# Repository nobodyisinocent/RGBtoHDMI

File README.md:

# Table of contents
1. [What is the RGBtoHDMI board](#1)
2. [Tiny RGB2HDMI CPLD design](#2)
3. [Low profile board based on design from c0pperdragon](#3)
    1. [CTDV board !](#3.1)
    2. [AMIGA 500 boards](#3.2)

# What is the RGBtoHDMI board 
The RGBtoHDMI device adds an HDMI output to your AMIGA only in OCS display mode thanks to the use of a Raspberry Pi0.
The very first RGB2HDMI design has been made by c0pperdragon. It can be found here:

https://github.com/c0pperdragon/Amiga-Digital-Video/

Originally, I made my own version since I wanted the smallest possible pcb for my personnal use, and also for the use of my friend Lolof.
The aim of these designs is to allow the combined use of the RGB2HDMI and others expansions as accelerator boards for example like the big board of the Mega Midget Racer.

Here, you'll find the three lowprofile following versions of the RGBtoHDMI I designed with Kicad and FreeRooting under Linux.

# Tiny RGB2HDMI CPLD design 
Always with the same goal, as small as possible, this board uses the CPLD Rev1.1 design from solarmon. But, since the configuration menu is accessible with one button, the 3 buttons and the OSD connector (no interest for my use) have been removed.

The firmware can be downloaded onto the official Github of the original CPLD version from hoglet67 here:

https://github.com/hoglet67/RGBtoHDMI/releases

To install the firmware, as for the first version of the RGBtoHDMI, simply extract the files to the µ-SD card's root and follow the instruction from Amiga_Readme.txt inside the Amiga_CPLD_Setup directory.

Here some pictures from Lolof of the Tiny CPLD RGBtoHDMI installed onto an A500 with the excellent TK030 from Matze !

# Low profile board based on design from c0pperdragon 

## CDTV board 

Here is the version specially designed for the CDTV.
The goal is always the same,having a nice and small board. :-)

## AMIGA 500 boards 

Two designs versions have been done. Here they are:

First design with Pi0 located between CIA and PAULA:

Second version, the smallest design version with the Pi0 installed just onto CIA with HDMI output on the back of the AMIGA.
It was special request of my friend Lolof, and perhaps the best one of the two A500 design:

And some pictures from Lolof of this second version rgb2hdmi in action onto his A500 !

And the first version onto my A500+ Red edition used with the Vampire V2+!

I hope you'll enjoy these versions of this great device !

-Tuxbar81

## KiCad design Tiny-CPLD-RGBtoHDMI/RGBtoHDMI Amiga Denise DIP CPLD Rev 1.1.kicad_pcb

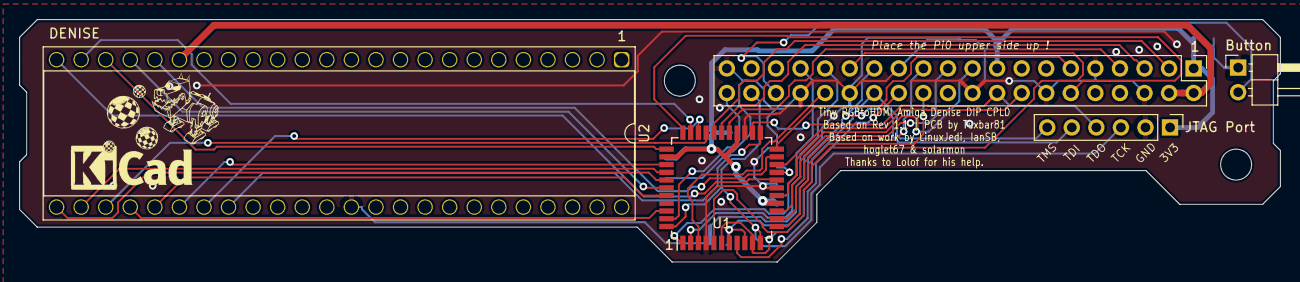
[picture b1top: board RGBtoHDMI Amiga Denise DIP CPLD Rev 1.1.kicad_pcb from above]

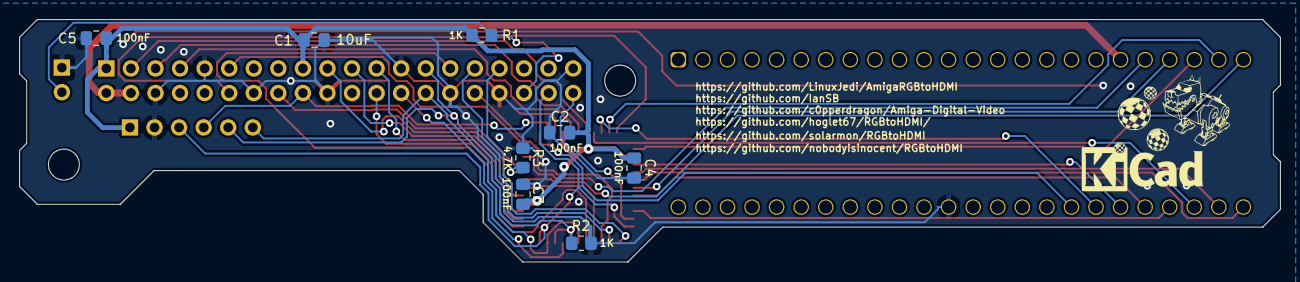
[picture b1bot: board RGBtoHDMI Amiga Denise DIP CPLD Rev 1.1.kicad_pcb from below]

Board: 2 copper layers, 130.3 x 25.1 mm, 13 parts (8 on the bottom side), 38 nets.

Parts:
Button: Jumper_2_Open; PinHeader_1x02_P2.54mm_Horizontal
C1: 10uF; C_0805_2012Metric_Pad1.18x1.45mm_HandSolder
C2, C3, C4, C5: 100nF; C_0805_2012Metric_Pad1.18x1.45mm_HandSolder
J1: Raspberry_Pi_2_3; PinSocket_2x20_P2.54mm_Vertical
JTAG Port: Pin_Header_Straight_1x06_Pitch2.54mm
R1, R2: 1K; R_0805_2012Metric_Pad1.20x1.40mm_HandSolder
R3: 4.7K; R_0805_2012Metric_Pad1.20x1.40mm_HandSolder
U1: XC9572VQ44 or XC9572XL-10VQG44C; TQFP-44_10x10mm_P0.8mm
U2: DENISE; DIP-48_W15.24mm_Socket

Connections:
+3V3: C1.1, C2.1, C3.1, C4.1, C5.1, J1.1, J1.17, JTAG Port.1, R1.1, U1.15, U1.26, U1.35
+5V: J1.2, J1.4, U2.19
/B0: U1.18, U2.24
/B1: U1.38, U2.25
/B2: U1.37, U2.26
/B3: U1.30, U2.27
/CLKEN: J1.28, JTAG Port.6, U1.6, U1.10
/CSYNC: U1.23, U2.32
/DETECT: R3.1, U1.19
/G0: U1.42, U2.28
/G1: U1.40, U2.29
/G2: U1.36, U2.30
/G3: U1.31, U2.31
/GPIO0: J1.27, JTAG Port.5, R2.1, U1.7, U1.9
/GPIO2: J1.3, U1.29
/GPIO3: J1.5, U1.28
/GPIO4: J1.7, U1.27
/GPIO5: J1.29, U1.5
/GPIO6: J1.31, U1.2
/GPIO7: J1.26, U1.8
/GPIO8: J1.24, U1.12
/GPIO9: J1.21, U1.14
/GPIO10: J1.19, U1.16
/GPIO11: J1.23, U1.13
/GPIO12: J1.32, U1.3
/GPIO13: J1.33, U1.1
/GPIO16: Button.2, J1.36, R1.2
/GPIO17: J1.11, U1.22
/GPIO18: J1.12, U1.33
/GPIO20: J1.38, JTAG Port.3, U1.11, U1.44
/GPIO21: J1.40, U1.43
/GPIO23: J1.16, U1.20
/GPIO24: J1.18, JTAG Port.4, U1.24
/R0: U1.21, U2.20
/R1: U1.39, U2.21
/R2: U1.34, U2.22
/R3: U1.32, U2.23
GND: Button.1, C1.2, C2.2, C3.2, C4.2, C5.2, J1.6, J1.9, J1.14, J1.20, J1.25, J1.30, J1.34, J1.39, JTAG Port.2, R2.2, R3.2, U1.4, U1.17, U1.25, U2.37

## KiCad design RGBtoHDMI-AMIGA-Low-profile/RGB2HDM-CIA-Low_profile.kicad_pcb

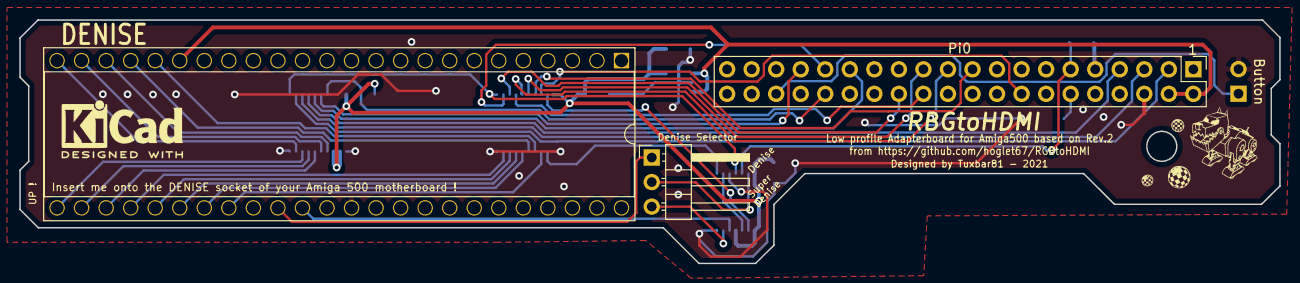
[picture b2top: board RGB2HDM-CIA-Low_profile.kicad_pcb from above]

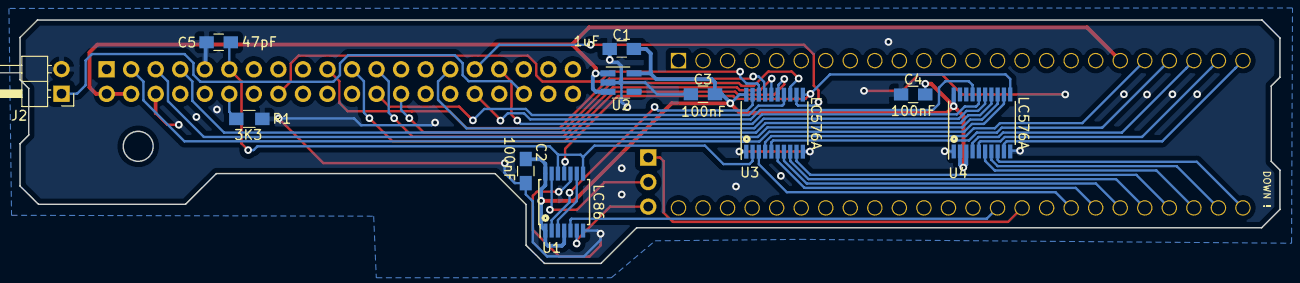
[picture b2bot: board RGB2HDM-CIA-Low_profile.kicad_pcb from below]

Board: 2 copper layers, 130.4 x 25.2 mm, 14 parts (11 on the bottom side), 39 nets.

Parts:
C1: 1uF; C_0805_HandSoldering
C2, C3, C4: 100nF; C_0805_HandSoldering
C5: 47pF; C_0805_HandSoldering
DENISE: DENISE_DIP-LABEL; DIP-48_W15.24mm_Socket
Denise Selector: JUMPER3; Pin_Header_Angled_1x03_Pitch2.54mm
J2: Conn_01x02; Pin_Header_Angled_1x02_Pitch2.54mm
Pi0: Conn_02x20_Odd_Even; Pin_Header_Straight_2x20_Pitch2.54mm
R1: 3K3; R_0805_HandSoldering
U1: LC86; TSSOP-14_4.4x5mm_Pitch0.65mm
U2: TLV70033_SOT23-5; SOT-23-5_HandSoldering
U3, U4: LC576A; TSSOP-20_4.4x6.5mm_Pitch0.65mm

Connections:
7M: DENISE.35, U1.5
+3V3: C1.1, C2.1, C3.1, C4.1, U1.1, U1.4, U1.14, U2.5, U3.20, U4.2, U4.3, U4.20
+5V: DENISE.19, Pi0.2, Pi0.4, U2.1, U2.3
B0: DENISE.24, U4.9
B1: DENISE.25, U4.8
B2: DENISE.26, U4.7
B3: DENISE.27, U4.6
BLANK: DENISE.32, U3.3
CDAC: DENISE.34, Denise Selector.1
G0: DENISE.28, U3.9
G1: DENISE.29, U3.8
G2: DENISE.30, U3.7
G3: DENISE.31, U3.6
GND: C1.2, C2.2, C3.2, C4.2, C5.2, DENISE.37, J2.2, Pi0.6, Pi0.9, R1.2, U1.7, U1.10, U2.2, U3.1, U3.10, U4.1, U4.10
unnamed: Pi0.12, R1.1
unnamed: J2.1, Pi0.36
unnamed: Denise Selector.2, U1.13
unnamed: Denise Selector.3, U1.6
unnamed: U1.2, U3.19
unnamed: U1.3, U1.9
unnamed: U1.11, U3.11, U4.11
PIB0: Pi0.3, U4.12
PIB1: Pi0.5, U4.13
PIB2: Pi0.7, U4.14
PIB3: Pi0.29, U4.15
PIBLANK: Pi0.16, U3.18
PICLK: C5.1, Pi0.11, U1.8, U1.12, U3.2
PIG0: Pi0.31, U3.12
PIG1: Pi0.26, U3.13
PIG2: Pi0.24, U3.14
PIG3: Pi0.21, U3.15
PIR0: Pi0.19, U3.17
PIR1: Pi0.23, U3.16
PIR2: Pi0.32, U4.17
PIR3: Pi0.33, U4.16
R0: DENISE.20, U3.4
R1: DENISE.21, U3.5
R2: DENISE.22, U4.4
R3: DENISE.23, U4.5
